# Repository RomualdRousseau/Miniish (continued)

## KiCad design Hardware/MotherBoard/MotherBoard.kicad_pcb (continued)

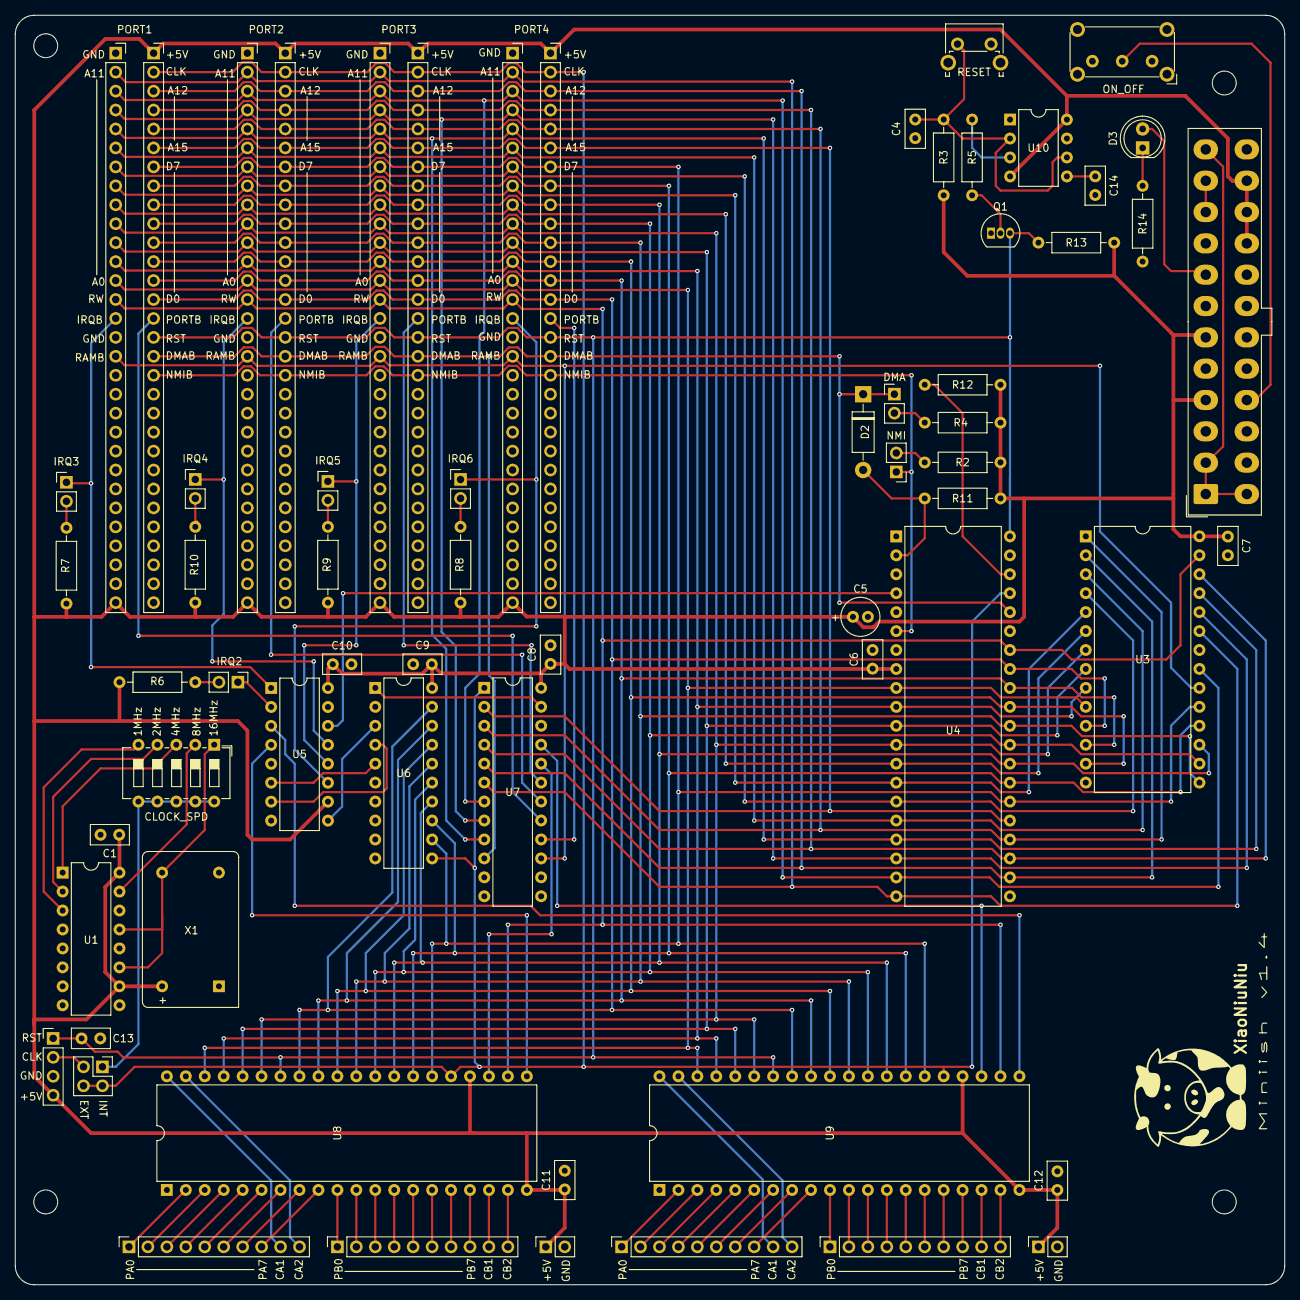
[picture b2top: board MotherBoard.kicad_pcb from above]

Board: 2 copper layers, 170.2 x 170.2 mm, 66 parts (0 on the bottom side), 113 nets.

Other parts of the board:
H1, H2, H3, H4: MountingHole_Pad; MountingHole_3.2mm_M3
XiaoNiuNiu: LOGO; SmallCow

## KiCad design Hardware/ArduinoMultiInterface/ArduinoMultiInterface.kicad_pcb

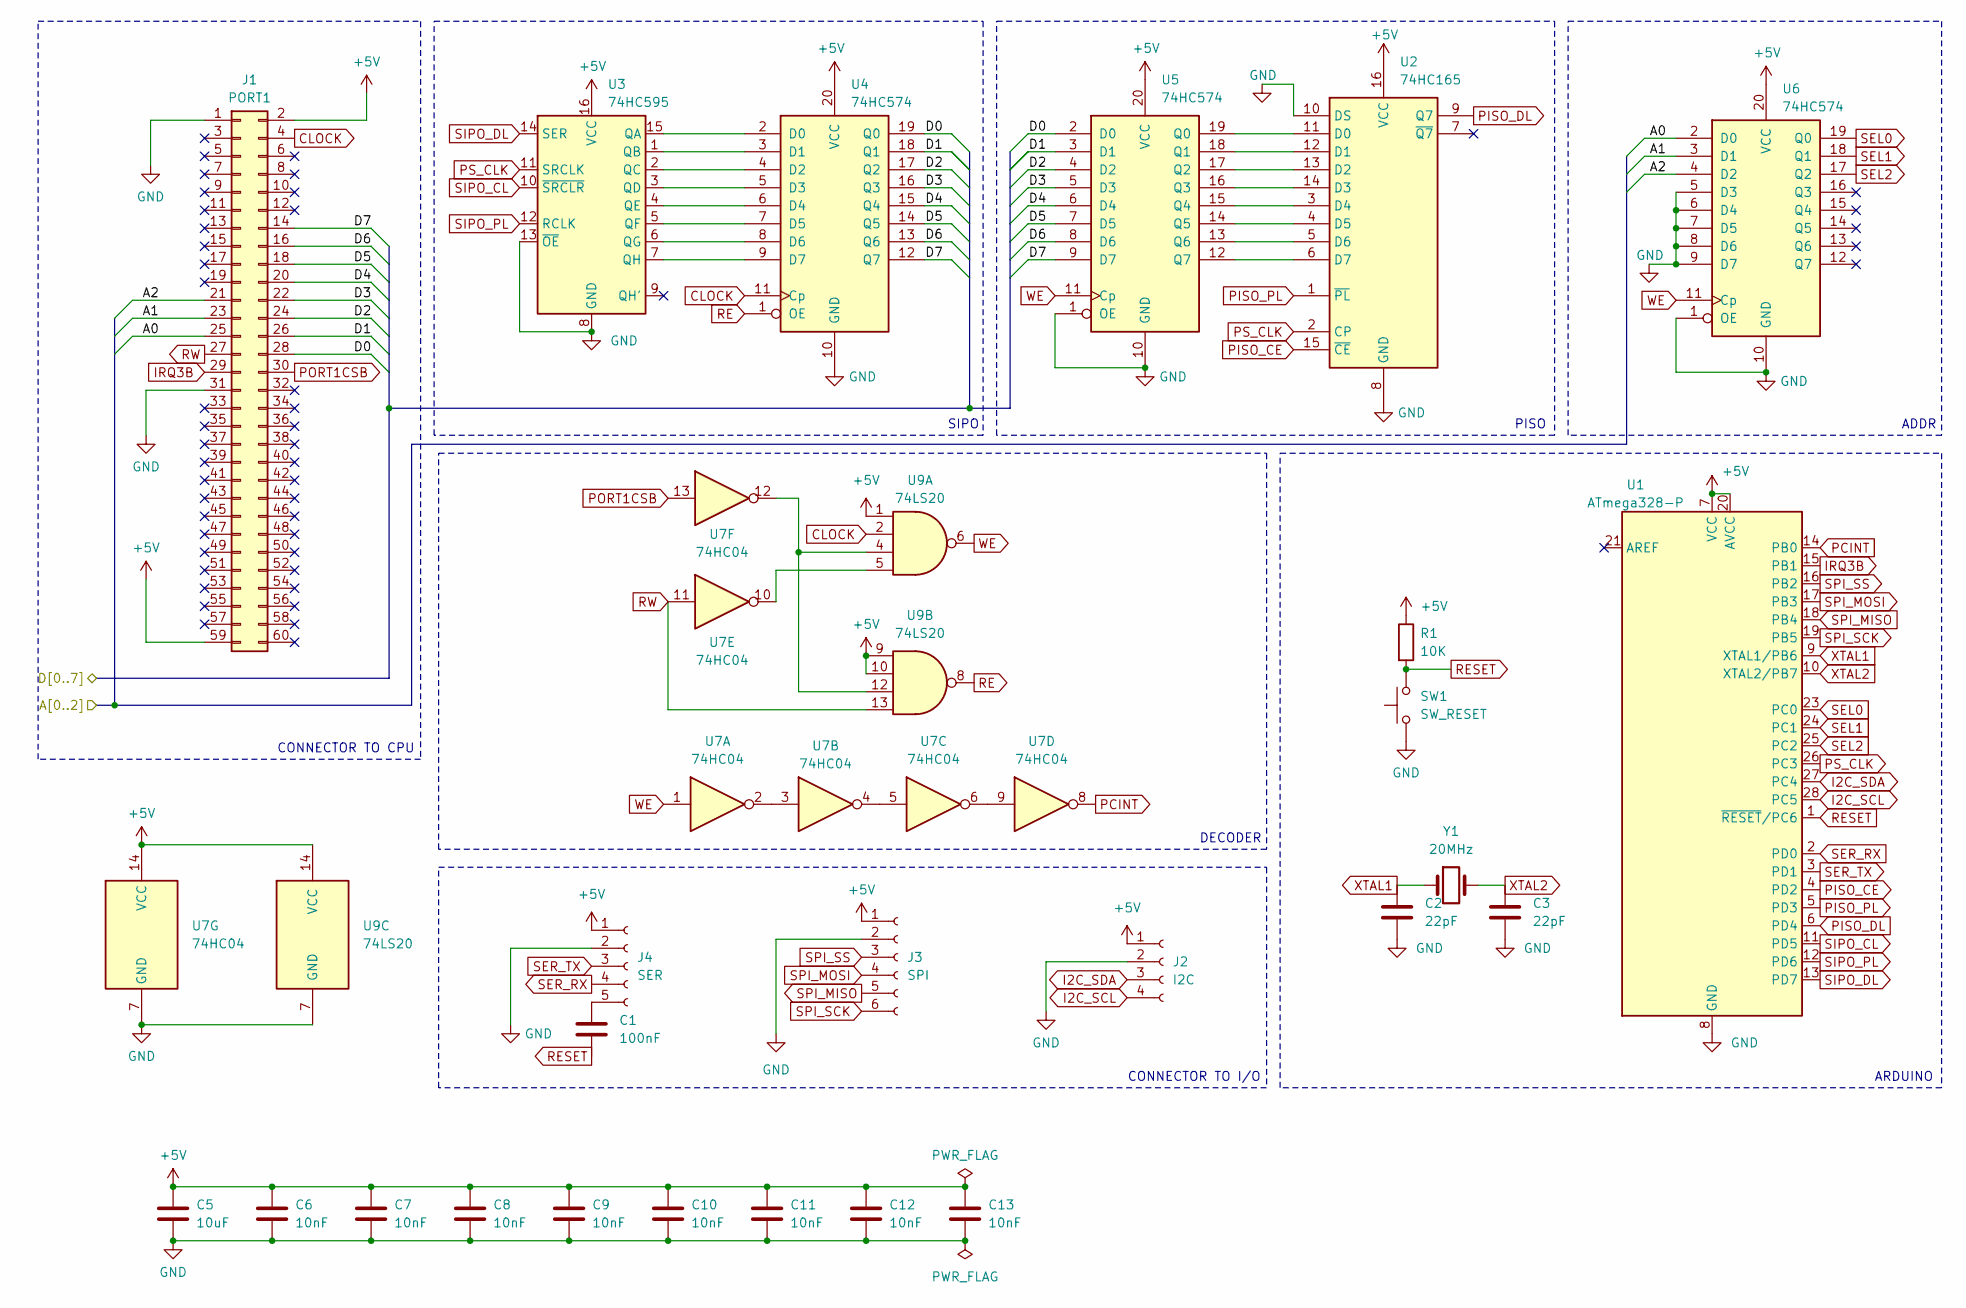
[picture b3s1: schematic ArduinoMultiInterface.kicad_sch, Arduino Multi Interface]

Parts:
C1: 100nF; C_Disc_D5.0mm_W2.5mm_P2.50mm
C2, C3: 22pF; C_Disc_D5.0mm_W2.5mm_P2.50mm
C5: 10uF; CP_Radial_D5.0mm_P2.00mm
C6, C7, C8, C9, C10, C11, C12, C13: 10nF; C_Disc_D5.0mm_W2.5mm_P5.00mm
J1: PORT1; NES_PCBEdge
J2: I2C; PinSocket_1x04_P2.54mm_Vertical
J3: SPI; PinSocket_1x06_P2.54mm_Vertical
J4: SER; PinSocket_1x05_P2.54mm_Vertical
R1: 10K; R_Axial_DIN0207_L6.3mm_D2.5mm_P10.16mm_Horizontal
SW1: SW_RESET; SW_PUSH_6mm
U1: ATmega328-P; DIP-28_W7.62mm
U2: 74HC165; DIP-16_W7.62mm
U3: 74HC595; DIP-16_W7.62mm
U4, U5, U6: 74HC574; DIP-20_W7.62mm
U7: 74HC04; DIP-14_W7.62mm
U9: 74LS20; DIP-14_W7.62mm
Y1: 20MHz; Crystal_HC49-4H_Vertical

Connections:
+5V: C5.1, C6.1, C7.1, C8.1, C9.1, C10.1, C11.1, C12.1, C13.1, J1.2, J1.59, J2.1, J3.1, J4.1, R1.1, U1.7 (VCC), U1.20 (AVCC), U2.16 (VCC), U3.16 (VCC), U4.20 (VCC), U5.20 (VCC), U6.20 (VCC), U7.14 (VCC), U9.1, U9.9, U9.10, U9.14 (VCC)
/A0: J1.25, U6.2 (D0)
/A1: J1.23, U6.3 (D1)
/A2: J1.21, U6.4 (D2)
/D0: J1.28, U4.19 (Q0), U5.2 (D0)
/D1: J1.26, U4.18 (Q1), U5.3 (D1)
/D2: J1.24, U4.17 (Q2), U5.4 (D2)
/D3: J1.22, U4.16 (Q3), U5.5 (D3)
/D4: J1.20, U4.15 (Q4), U5.6 (D4)
/D5: J1.18, U4.14 (Q5), U5.7 (D5)
/D6: J1.16, U4.13 (Q6), U5.8 (D6)
/D7: J1.14, U4.12 (Q7), U5.9 (D7)
CLOCK: J1.4, U4.11 (Cp), U9.2
GND: C2.2, C3.2, C5.2, C6.2, C7.2, C8.2, C9.2, C10.2, C11.2, C12.2, C13.2, J1.1, J1.31, J2.2, J3.2, J4.2, SW1.1, U1.8 (GND), U1.22 (GND), U2.8 (GND), U2.10 (DS), U3.8 (GND), U3.13 (~OE), U4.10 (GND), U5.1 (OE), U5.10 (GND), U6.1 (OE), U6.5 (D3), U6.6 (D4), U6.7 (D5), U6.8 (D6), U6.9 (D7), U6.10 (GND), U7.7 (GND), U9.7 (GND)
I2C_SCL: J2.4, U1.28 (PC5)
I2C_SDA: J2.3, U1.27 (PC4)
IRQ3B: J1.29, U1.15 (PB1)
unnamed: C1.1, J4.5
unnamed: U2.11 (D0), U5.19 (Q0)
unnamed: U2.12 (D1), U5.18 (Q1)
unnamed: U2.13 (D2), U5.17 (Q2)
unnamed: U2.14 (D3), U5.16 (Q3)
unnamed: U2.3 (D4), U5.15 (Q4)
unnamed: U2.4 (D5), U5.14 (Q5)
unnamed: U2.5 (D6), U5.13 (Q6)
unnamed: U2.6 (D7), U5.12 (Q7)
unnamed: U3.15 (QA), U4.2 (D0)
unnamed: U3.1 (QB), U4.3 (D1)
unnamed: U3.2 (QC), U4.4 (D2)
unnamed: U3.3 (QD), U4.5 (D3)
unnamed: U3.4 (QE), U4.6 (D4)
unnamed: U3.5 (QF), U4.7 (D5)
unnamed: U3.6 (QG), U4.8 (D6)
unnamed: U3.7 (QH), U4.9 (D7)
unnamed: U7.2, U7.3
unnamed: U7.4, U7.5
unnamed: U7.6, U7.9
unnamed: U7.10, U9.5
unnamed: U7.12, U9.4, U9.12
PCINT: U1.14 (PB0), U7.8
PISO_CE: U1.4 (PD2), U2.15 (~CE)
PISO_DL: U1.6 (PD4), U2.9 (Q7)
PISO_PL: U1.5 (PD3), U2.1 (~PL)
PORT1CSB: J1.30, U7.13
PS_CLK: U1.26 (PC3), U2.2 (CP), U3.11 (SRCLK)
RE: U4.1 (OE), U9.8
RESET: C1.2, R1.2, SW1.2, U1.1 (~RESET/PC6)
RW: J1.27, U7.11, U9.13
SEL0: U1.23 (PC0), U6.19 (Q0)
SEL1: U1.24 (PC1), U6.18 (Q1)
SEL2: U1.25 (PC2), U6.17 (Q2)
SER_RX: J4.4, U1.2 (PD0)
SER_TX: J4.3, U1.3 (PD1)
SIPO_CL: U1.11 (PD5), U3.10 (~SRCLR)
SIPO_DL: U1.13 (PD7), U3.14 (SER)
SIPO_PL: U1.12 (PD6), U3.12 (RCLK)
SPI_MISO: J3.5, U1.18 (PB4)
SPI_MOSI: J3.4, U1.17 (PB3)
SPI_SCK: J3.6, U1.19 (PB5)
SPI_SS: J3.3, U1.16 (PB2)
WE: U5.11 (Cp), U6.11 (Cp), U7.1, U9.6
XTAL1: C2.1, U1.9 (XTAL1/PB6), Y1.1
XTAL2: C3.1, U1.10 (XTAL2/PB7), Y1.2

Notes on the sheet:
CONNECTOR TO CPU
ARDUINO
PISO
DECODER
SIPO
ADDR
CONNECTOR TO I/O

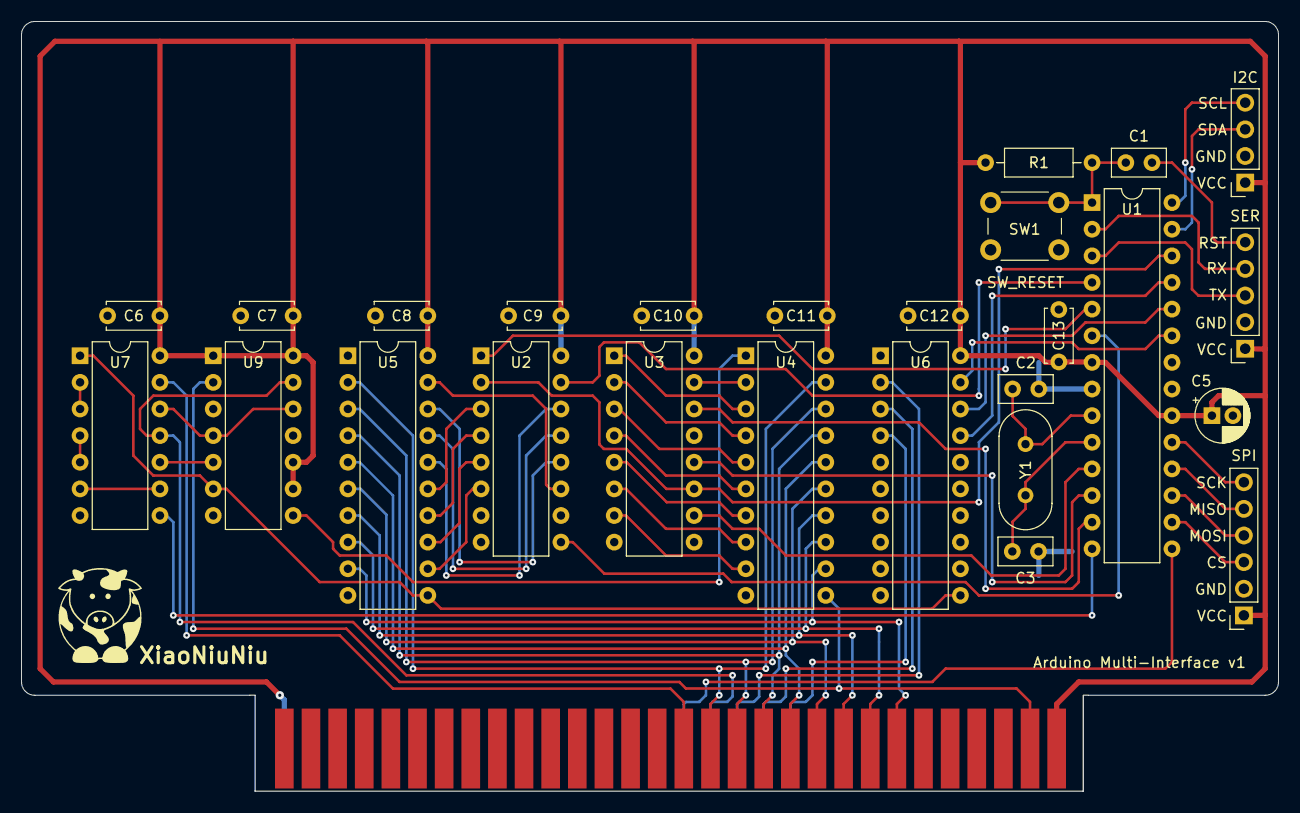
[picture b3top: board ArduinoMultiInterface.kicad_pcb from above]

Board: 2 copper layers, 119.9 x 73.4 mm, 28 parts (0 on the bottom side), 63 nets.

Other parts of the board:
XiaoNiuNiu: LOGO; VerySmallCow

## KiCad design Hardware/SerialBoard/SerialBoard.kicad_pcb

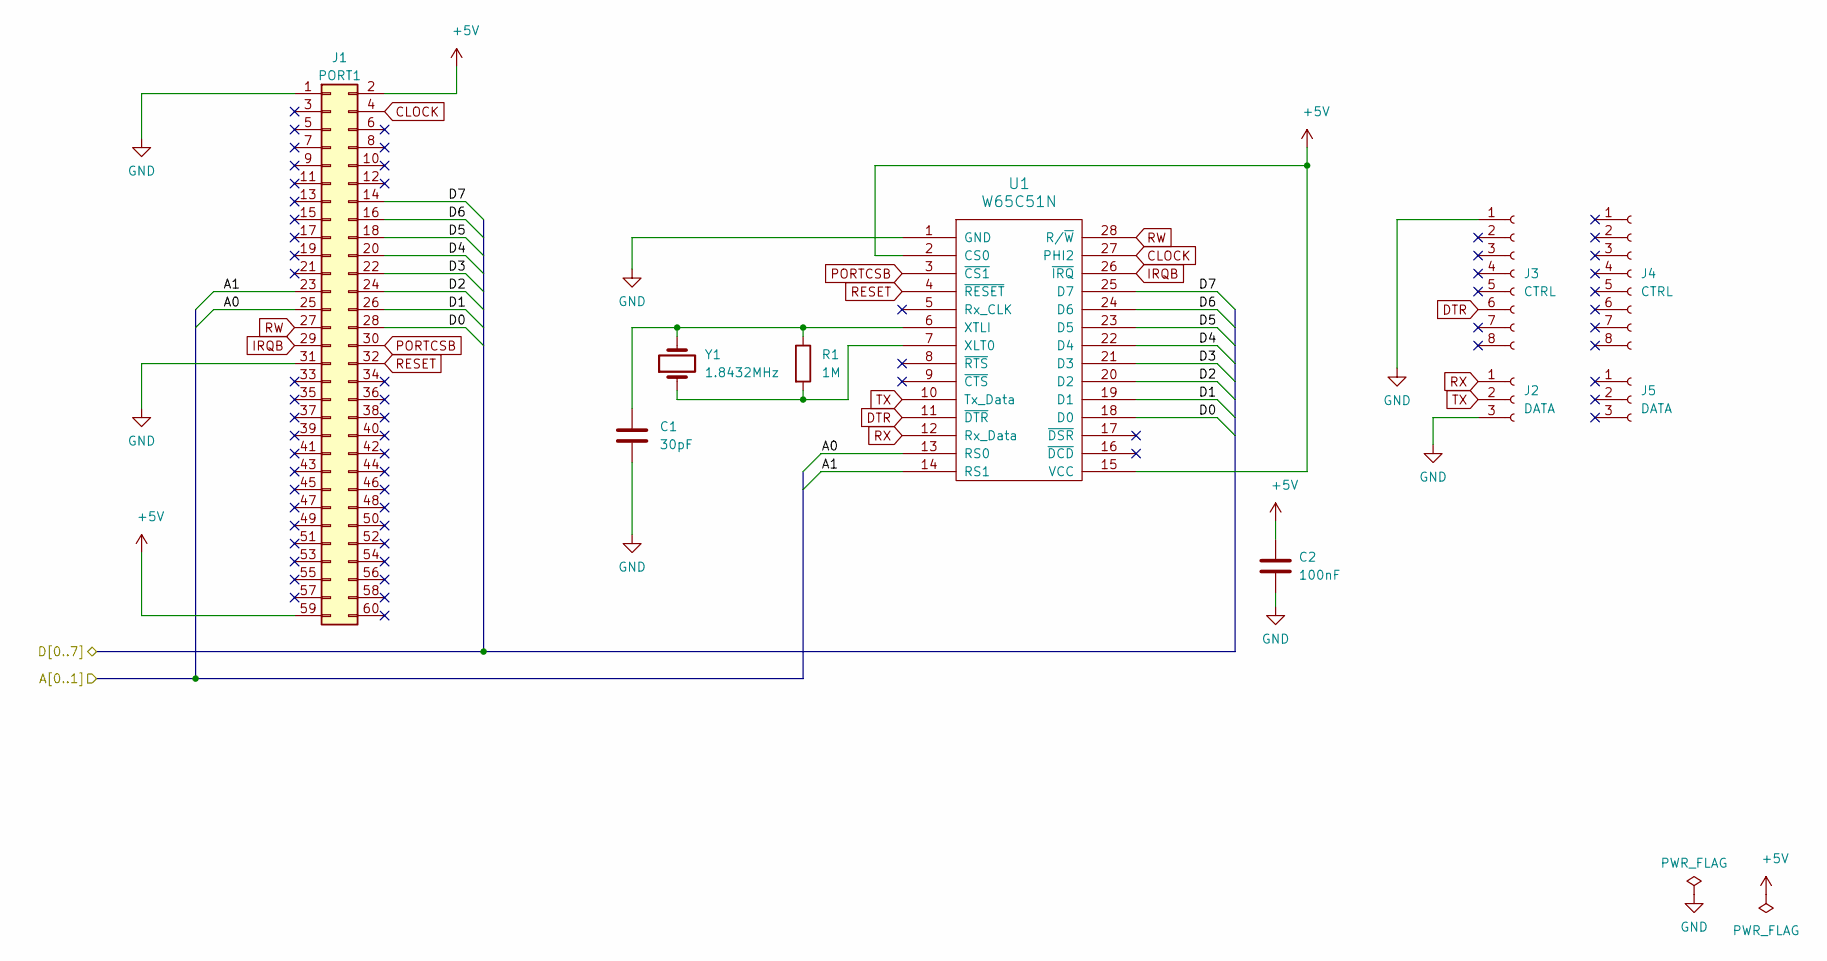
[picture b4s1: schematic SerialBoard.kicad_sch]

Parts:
C1: 30pF; C_Disc_D5.0mm_W2.5mm_P2.50mm
C2: 100nF; C_Disc_D5.0mm_W2.5mm_P2.50mm
J1: PORT1; NES_PCBEdge
J2, J5: DATA; PinSocket_1x03_P2.54mm_Vertical
J3, J4: CTRL; PinSocket_1x08_P2.54mm_Vertical
R1: 1M; R_Axial_DIN0207_L6.3mm_D2.5mm_P10.16mm_Horizontal
U1: W65C51N; DIP-28_W15.24mm
Y1: 1.8432MHz; Crystal_HC49-4H_Vertical

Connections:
+5V: C2.1, J1.2, J1.59, U1.2 (CS0), U1.15 (VCC)
/A0: J1.25, U1.13 (RS0)
/A1: J1.23, U1.14 (RS1)
/D0: J1.28, U1.18 (D0)
/D1: J1.26, U1.19 (D1)
/D2: J1.24, U1.20 (D2)
/D3: J1.22, U1.21 (D3)
/D4: J1.20, U1.22 (D4)
/D5: J1.18, U1.23 (D5)
/D6: J1.16, U1.24 (D6)
/D7: J1.14, U1.25 (D7)
CLOCK: J1.4, U1.27 (PHI2)
DTR: J3.6, U1.11 (~DTR)
GND: C1.2, C2.2, J1.1, J1.31, J2.3, J3.1, U1.1 (GND)
IRQB: J1.29, U1.26 (~IRQ)
unnamed: R1.2, U1.7 (XLT0), Y1.1
unnamed: C1.1, R1.1, U1.6 (XTLI), Y1.2
PORTCSB: J1.30, U1.3 (~CS1)
RESET: J1.32, U1.4 (~RESET)
RW: J1.27, U1.28 (R/~W)
RX: J2.1, U1.12 (Rx_Data)
TX: J2.2, U1.10 (Tx_Data)

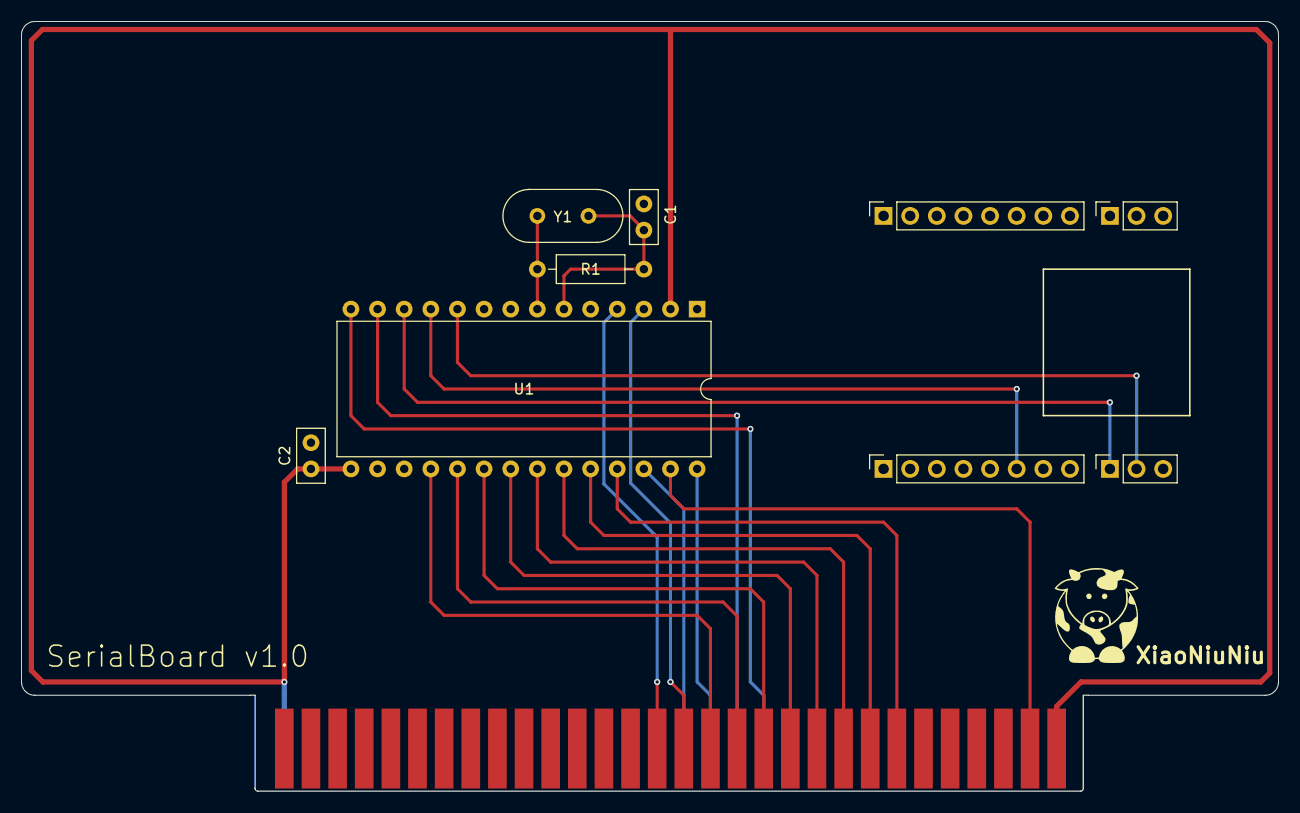
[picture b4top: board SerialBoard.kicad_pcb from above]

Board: 2 copper layers, 119.9 x 73.4 mm, 11 parts (0 on the bottom side), 22 nets.

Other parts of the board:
XiaoNiuNiu: LOGO; VerySmallCow

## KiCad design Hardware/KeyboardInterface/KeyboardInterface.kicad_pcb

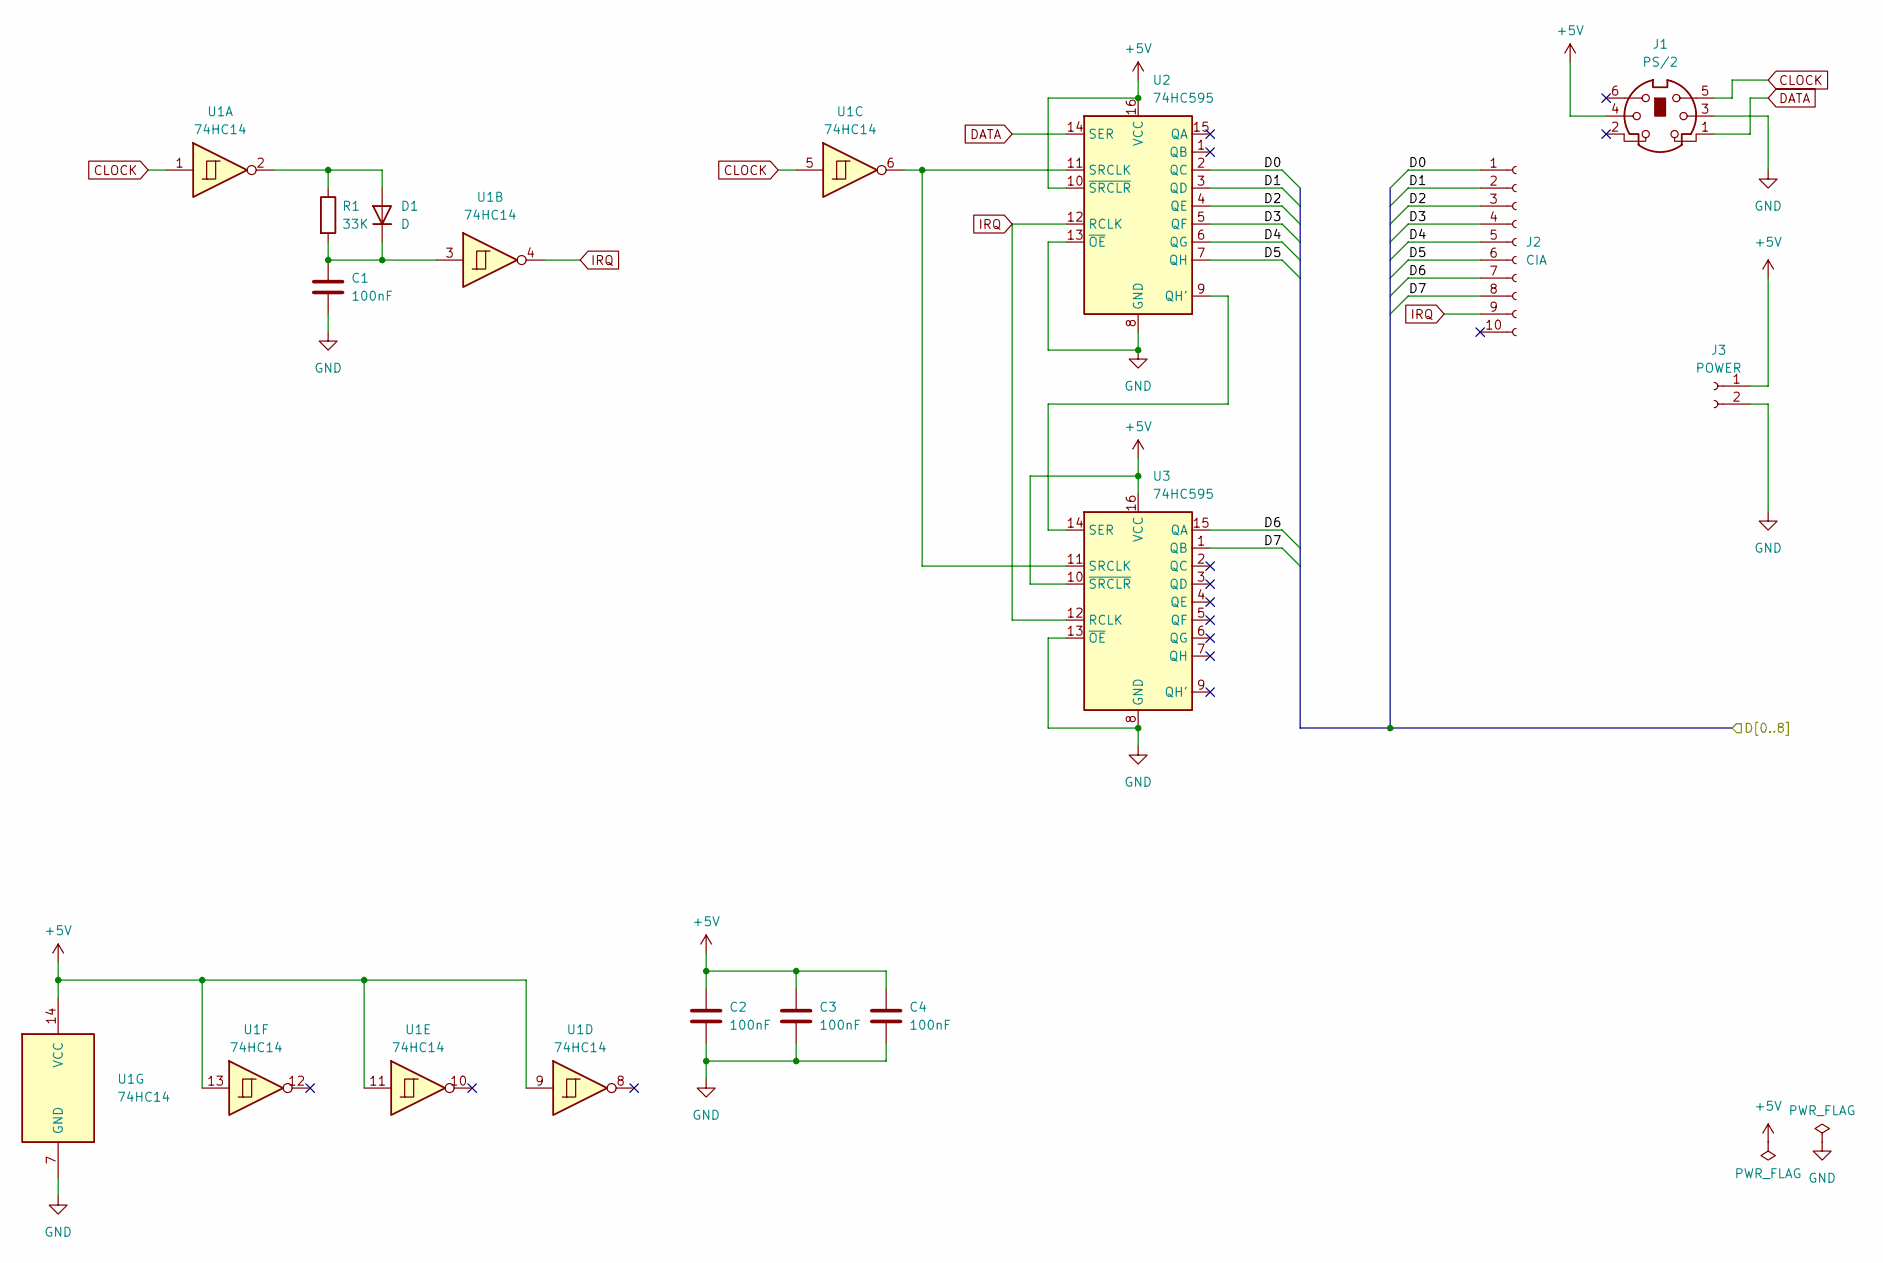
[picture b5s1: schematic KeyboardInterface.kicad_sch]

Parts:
C1, C2, C3, C4: 100nF; C_Disc_D5.0mm_W2.5mm_P2.50mm
D1: D; D_A-405_P10.16mm_Horizontal
J1: PS/2; Mini_din6
J2: CIA; PinSocket_1x10_P2.54mm_Vertical
J3: POWER; PinSocket_1x02_P2.54mm_Vertical
R1: 33K; R_Axial_DIN0309_L9.0mm_D3.2mm_P12.70mm_Horizontal
U1: 74HC14; DIP-14_W7.62mm
U2, U3: 74HC595; DIP-16_W7.62mm

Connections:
+5V: C2.1, C3.1, C4.1, J1.4, J3.1, U1.9, U1.11, U1.13, U1.14 (VCC), U2.10 (~SRCLR), U2.16 (VCC), U3.10 (~SRCLR), U3.16 (VCC)
/D0: J2.1, U2.2 (QC)
/D1: J2.2, U2.3 (QD)
/D2: J2.3, U2.4 (QE)
/D3: J2.4, U2.5 (QF)
/D4: J2.5, U2.6 (QG)
/D5: J2.6, U2.7 (QH)
/D6: J2.7, U3.15 (QA)
/D7: J2.8, U3.1 (QB)
CLOCK: J1.5, U1.1, U1.5
DATA: J1.1, U2.14 (SER)
GND: C1.2, C2.2, C3.2, C4.2, J1.3, J3.2, U1.7 (GND), U2.8 (GND), U2.13 (~OE), U3.8 (GND), U3.13 (~OE)
IRQ: J2.9, U1.4, U2.12 (RCLK), U3.12 (RCLK)
unnamed: D1.2 (A), R1.1, U1.2
unnamed: C1.1, D1.1 (K), R1.2, U1.3
unnamed: U2.9 (QH'), U3.14 (SER)
unnamed: U1.6, U2.11 (SRCLK), U3.11 (SRCLK)

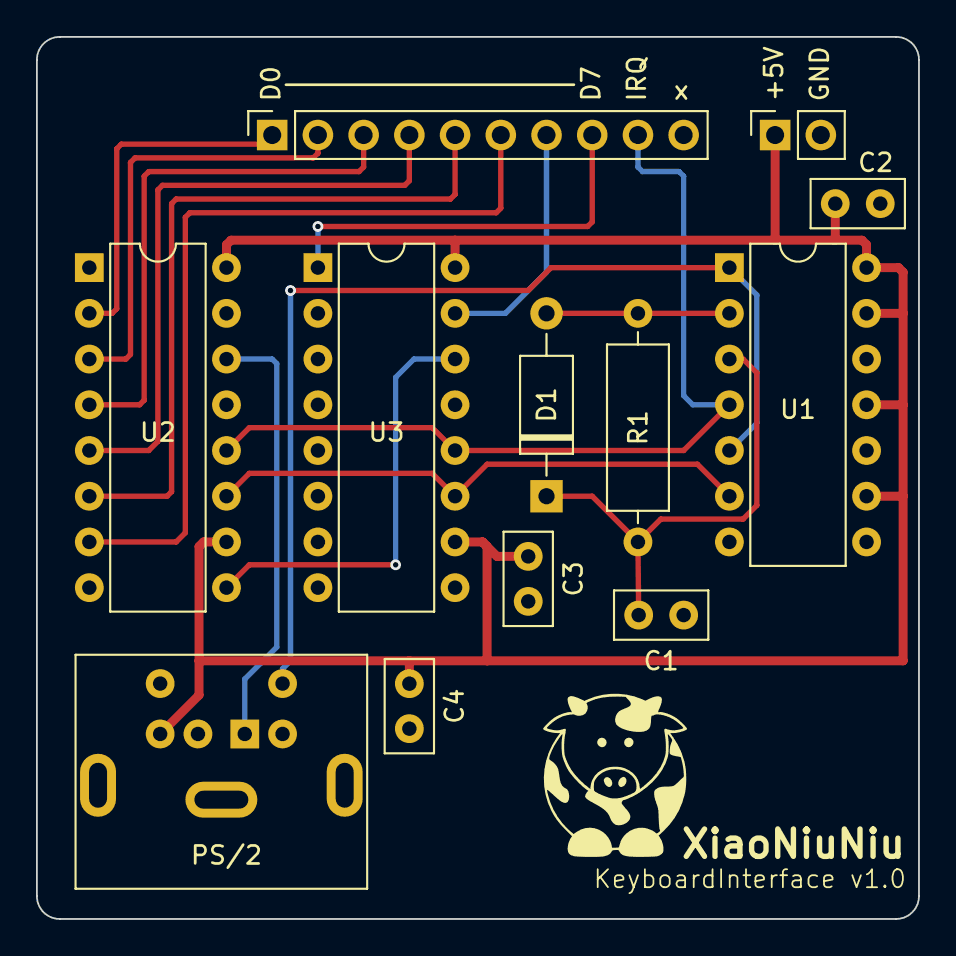
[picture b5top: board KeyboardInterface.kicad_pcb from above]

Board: 2 copper layers, 49.0 x 49.0 mm, 13 parts (0 on the bottom side), 17 nets.

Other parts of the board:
XiaoNiuNiu: LOGO; VerySmallCow

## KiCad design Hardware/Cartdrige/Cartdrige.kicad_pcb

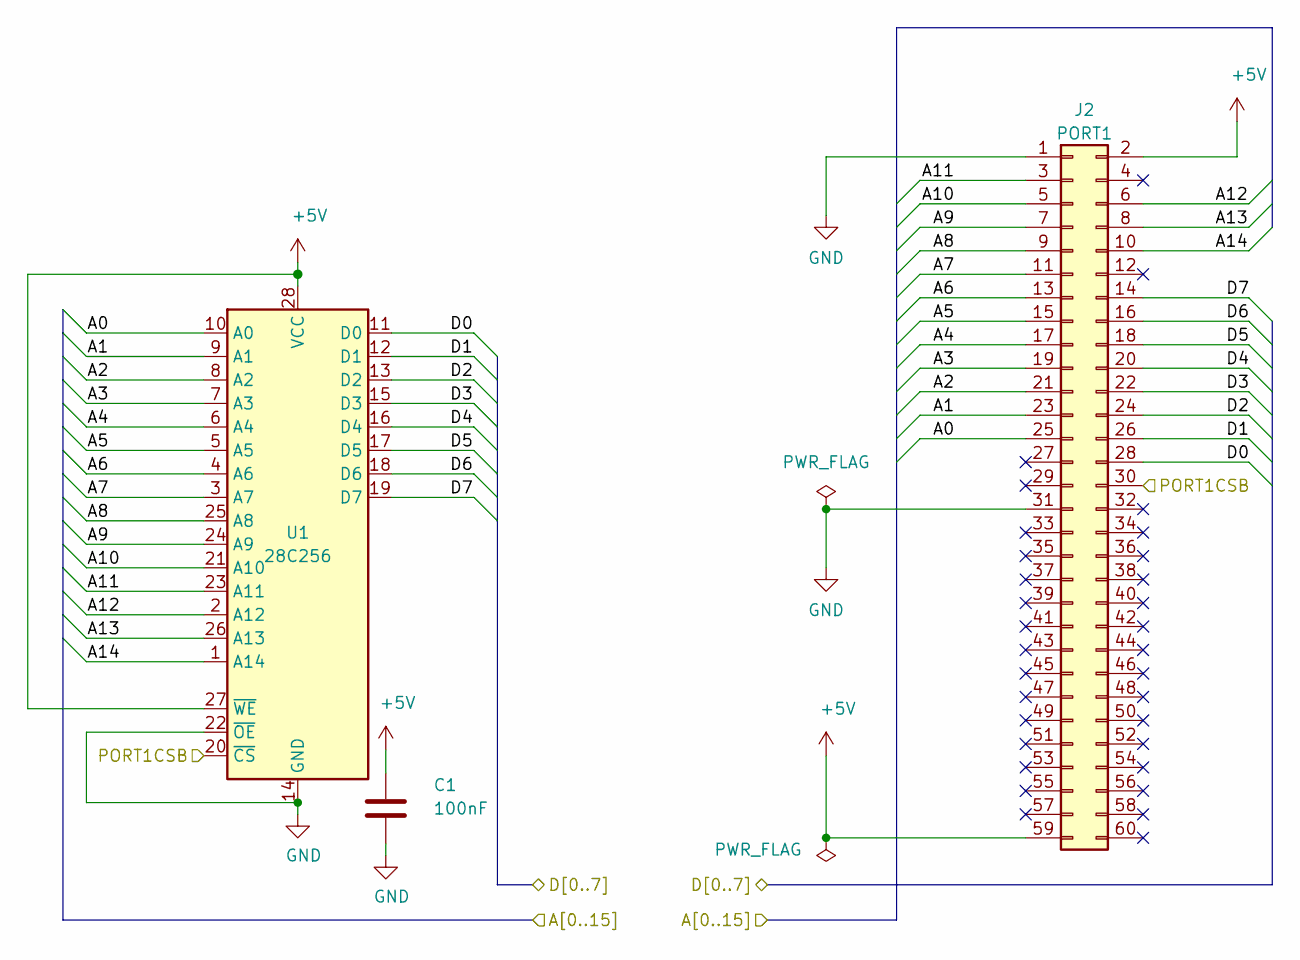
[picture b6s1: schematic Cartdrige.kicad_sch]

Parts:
C1: 100nF; C_Disc_D5.0mm_W2.5mm_P2.50mm
J2: PORT1; NES_PCBEdge
U1: 28C256; DIP-28_W15.24mm

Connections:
+5V: C1.1, J2.2, J2.59, U1.27 (~WE), U1.28 (VCC)
/A0: J2.25, U1.10 (A0)
/A1: J2.23, U1.9 (A1)
/A2: J2.21, U1.8 (A2)
/A3: J2.19, U1.7 (A3)
/A4: J2.17, U1.6 (A4)
/A5: J2.15, U1.5 (A5)
/A6: J2.13, U1.4 (A6)
/A7: J2.11, U1.3 (A7)
/A8: J2.9, U1.25 (A8)
/A9: J2.7, U1.24 (A9)
/A10: J2.5, U1.21 (A10)
/A11: J2.3, U1.23 (A11)
/A12: J2.6, U1.2 (A12)
/A13: J2.8, U1.26 (A13)
/A14: J2.10, U1.1 (A14)
/A15: J2.12
/CLOCK: J2.4
/D0: J2.28, U1.11 (D0)
/D1: J2.26, U1.12 (D1)
/D2: J2.24, U1.13 (D2)
/D3: J2.22, U1.15 (D3)
/D4: J2.20, U1.16 (D4)
/D5: J2.18, U1.17 (D5)
/D6: J2.16, U1.18 (D6)
/D7: J2.14, U1.19 (D7)
/DMAB: J2.34
/IRQ3B: J2.29
/NMIB: J2.36
/PORT1CSB: J2.30, U1.20 (~CS)
/RAMCSB: J2.33
/RESET: J2.32
/RW: J2.27
GND: C1.2, J2.1, J2.31, U1.14 (GND), U1.22 (~OE)

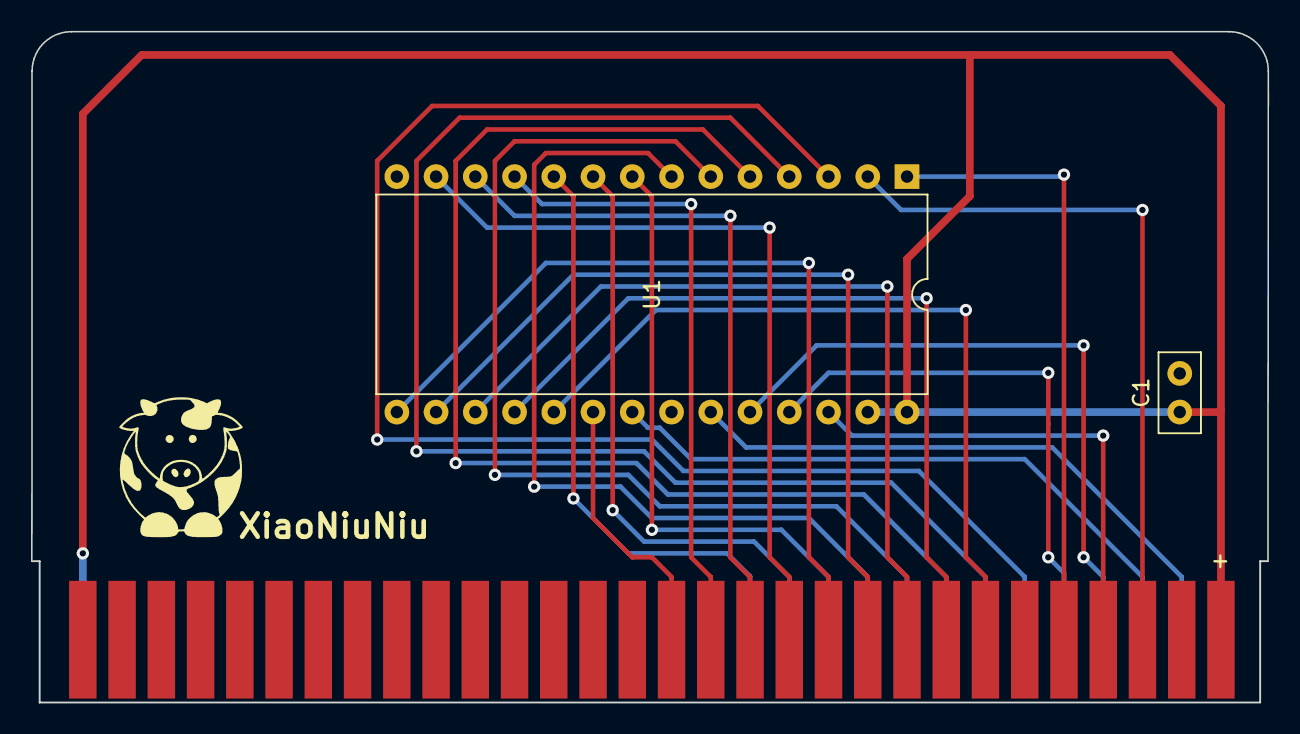
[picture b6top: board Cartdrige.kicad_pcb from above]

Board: 2 copper layers, 80.0 x 43.4 mm, 4 parts (0 on the bottom side), 26 nets.

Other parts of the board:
XiaoNiuNiu: LOGO; VerySmallCow

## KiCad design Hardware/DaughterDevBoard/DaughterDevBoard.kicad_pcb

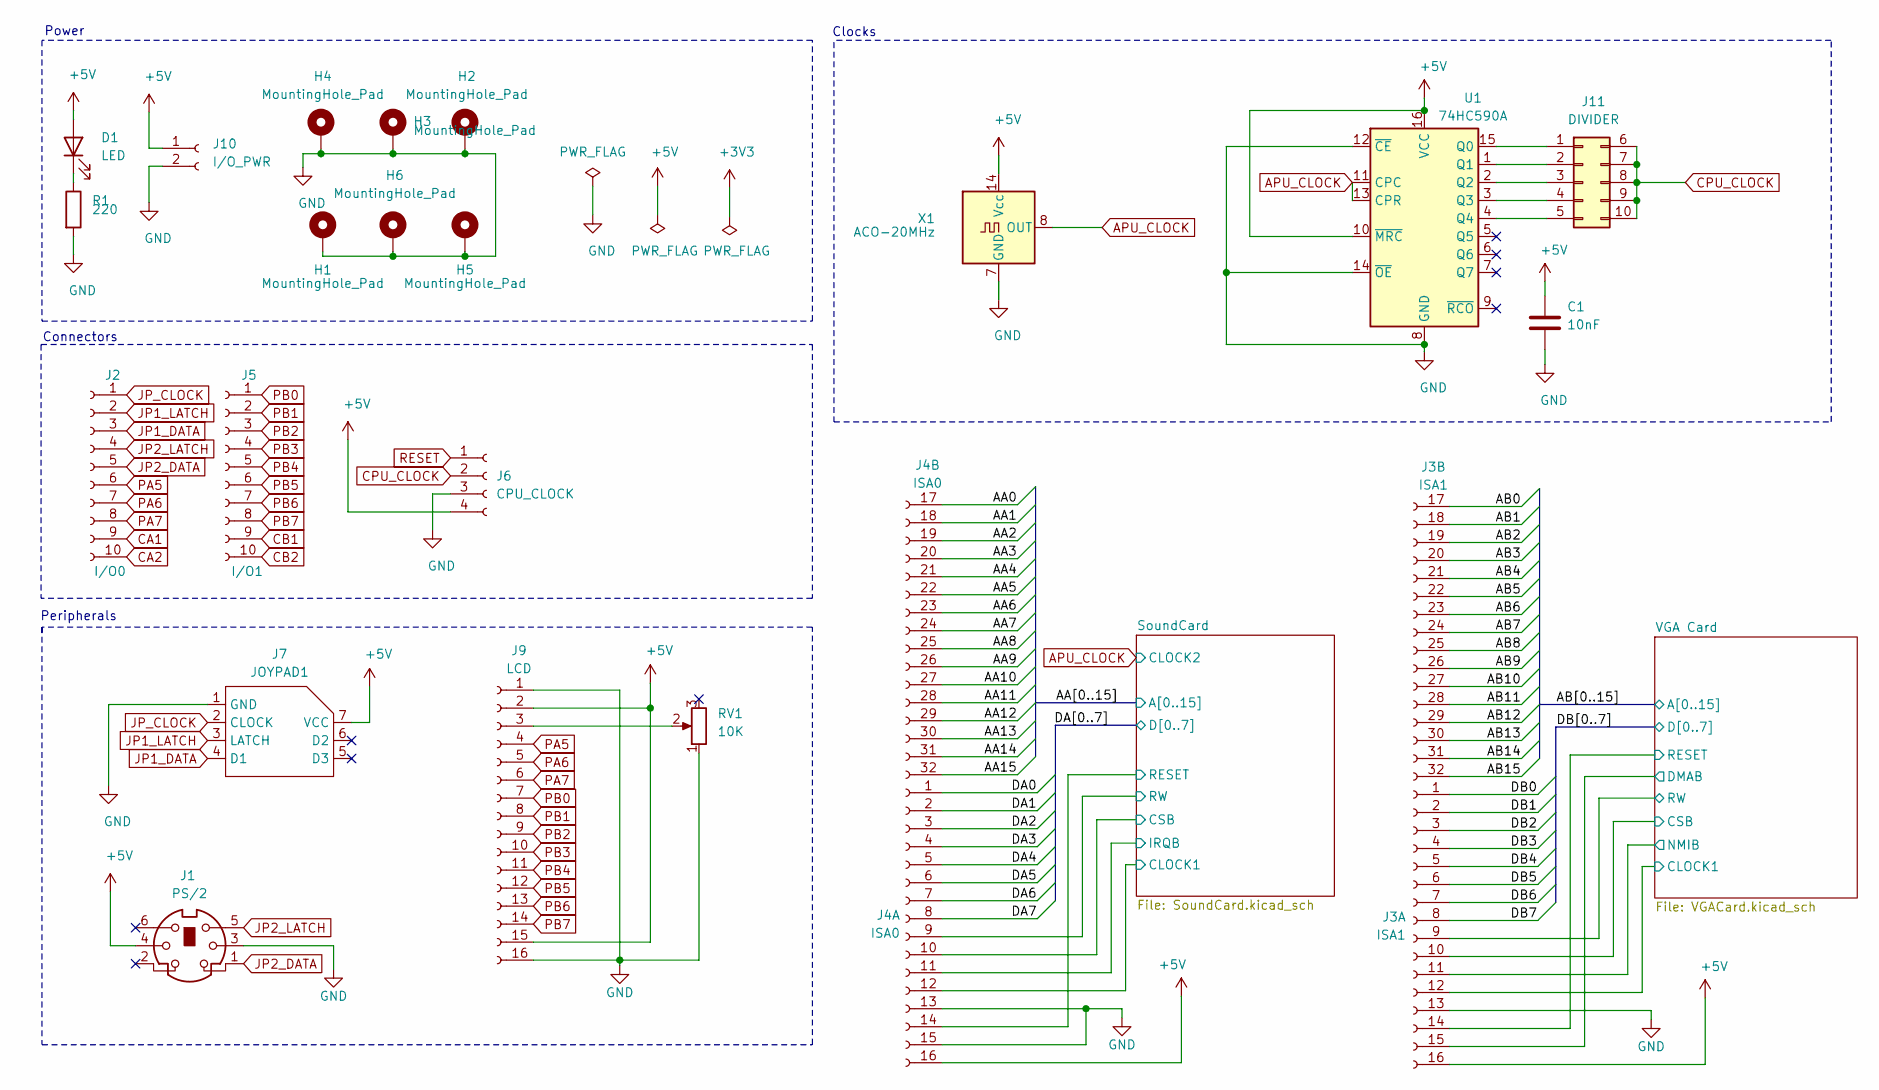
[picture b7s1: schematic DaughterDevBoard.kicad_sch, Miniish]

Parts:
C1: 10nF; C_Disc_D5.0mm_W2.5mm_P2.50mm
D1: LED; LED_D5.0mm
H1, H2, H3, H4, H5, H6: MountingHole_Pad; MountingHole_3.2mm_M3
J1: PS/2; Connector_Mini-DIN_Female_6Pin_2rows
J2: I/O0; PinHeader_1x10_P2.54mm_Vertical
J3: ISA1; PinHeader_2x16_P2.54mm_Vertical
J4: ISA0; PinHeader_2x16_P2.54mm_Vertical
J5: I/O1; PinHeader_1x10_P2.54mm_Vertical
J6: CPU_CLOCK; PinHeader_1x04_P2.54mm_Vertical
J7: JOYPAD1; NES_JoyPad
J9: LCD; PinSocket_1x16_P2.54mm_Vertical
J10: I/O_PWR; PinHeader_1x02_P2.54mm_Vertical
J11: DIVIDER; SW_DIP_SPSTx05_Slide_6.7x14.26mm_W7.62mm_P2.54mm_LowProfile
R1: 220; R_Axial_DIN0207_L6.3mm_D2.5mm_P10.16mm_Horizontal
RV1: 10K; Potentiometer_Bourns_3266Y_Vertical
U1: 74HC590A; DIP-16_W7.62mm
X1: ACO-20MHz; Oscillator_DIP-14

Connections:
+5V: C1.1, D1.2 (A), J1.4, J3.16, J4.16, J6.4, J7.7 (VCC), J9.2, J9.15, J10.1, U1.10 (~MRC), U1.16 (VCC), X1.14 (Vcc); also elsewhere on the board
/AA0: J4.17; also elsewhere on the board
/AA1: J4.18; also elsewhere on the board
/AA2: J4.19; also elsewhere on the board
/AA3: J4.20; also elsewhere on the board
/AA4: J4.21; also elsewhere on the board
/AA5: J4.22; also elsewhere on the board
/AA6: J4.23
/AA7: J4.24
/AA8: J4.25
/AA9: J4.26
/AA10: J4.27
/AA11: J4.28
/AA12: J4.29
/AA13: J4.30
/AA14: J4.31
/AA15: J4.32
/AB0: J3.17; also elsewhere on the board
/AB1: J3.18; also elsewhere on the board
/AB2: J3.19; also elsewhere on the board
/AB3: J3.20; also elsewhere on the board
/AB4: J3.21; also elsewhere on the board
/AB5: J3.22; also elsewhere on the board
/AB6: J3.23; also elsewhere on the board
/AB7: J3.24; also elsewhere on the board
/AB8: J3.25; also elsewhere on the board
/AB9: J3.26; also elsewhere on the board
/AB10: J3.27; also elsewhere on the board
/AB11: J3.28; also elsewhere on the board
/AB12: J3.29; also elsewhere on the board
/AB13: J3.30; also elsewhere on the board
/AB14: J3.31; also elsewhere on the board
/AB15: J3.32; also elsewhere on the board
/DA0: J4.1; also elsewhere on the board
/DA1: J4.2; also elsewhere on the board
/DA2: J4.3; also elsewhere on the board
/DA3: J4.4; also elsewhere on the board
/DA4: J4.5; also elsewhere on the board
/DA5: J4.6; also elsewhere on the board
/DA6: J4.7; also elsewhere on the board
/DA7: J4.8; also elsewhere on the board
/DB0: J3.1; also elsewhere on the board
/DB1: J3.2; also elsewhere on the board
/DB2: J3.3; also elsewhere on the board
/DB3: J3.4; also elsewhere on the board
/DB4: J3.5; also elsewhere on the board
/DB5: J3.6; also elsewhere on the board
/DB6: J3.7; also elsewhere on the board
/DB7: J3.8; also elsewhere on the board
/SoundCard/CLOCK1: J4.12; also elsewhere on the board
/SoundCard/CSB: J4.10; also elsewhere on the board
/SoundCard/IRQB: J4.11; also elsewhere on the board
/SoundCard/RESET: J4.14; also elsewhere on the board
/SoundCard/RW: J4.9; also elsewhere on the board
/VGA Card/CLOCK1: J3.12; also elsewhere on the board
/VGA Card/CSB: J3.10; also elsewhere on the board
/VGA Card/DMAB: J3.15; also elsewhere on the board
/VGA Card/NMIB: J3.11; also elsewhere on the board
/VGA Card/RESET: J3.14; also elsewhere on the board
/VGA Card/RW: J3.9; also elsewhere on the board
APU_CLOCK: U1.11 (CPC), U1.13 (CPR), X1.8 (OUT); also elsewhere on the board
CA1: J2.9
CA2: J2.10
CB1: J5.9
CB2: J5.10
CPU_CLOCK: J6.2, J11.6, J11.7, J11.8, J11.9, J11.10
GND: C1.2, H1.1, H2.1, H3.1, H4.1, H5.1, H6.1, J1.3, J3.13, J4.13, J4.15, J6.3, J7.1 (GND), J9.1, J9.16, J10.2, R1.2, RV1.1, U1.8 (GND), U1.12 (~CE), U1.14 (~OE), X1.7 (GND); also elsewhere on the board
JP1_DATA: J2.3, J7.4 (D1)
JP1_LATCH: J2.2, J7.3 (LATCH)
JP2_DATA: J1.1, J2.5
JP2_LATCH: J1.5, J2.4
JP_CLOCK: J2.1, J7.2 (CLOCK)
unnamed: D1.1 (K), R1.1
unnamed: J9.3, RV1.2
unnamed: J11.1, U1.15 (Q0)
unnamed: J11.2, U1.1 (Q1)
unnamed: J11.3, U1.2 (Q2)
unnamed: J11.4, U1.3 (Q3)
unnamed: J11.5, U1.4 (Q4)
PA5: J2.6, J9.4
PA6: J2.7, J9.5
PA7: J2.8, J9.6
PB0: J5.1, J9.7
PB1: J5.2, J9.8
PB2: J5.3, J9.9
PB3: J5.4, J9.10
PB4: J5.5, J9.11
PB5: J5.6, J9.12
PB6: J5.7, J9.13
PB7: J5.8, J9.14
RESET: J6.1

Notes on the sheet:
Power
Clocks
Peripherals
Connectors
